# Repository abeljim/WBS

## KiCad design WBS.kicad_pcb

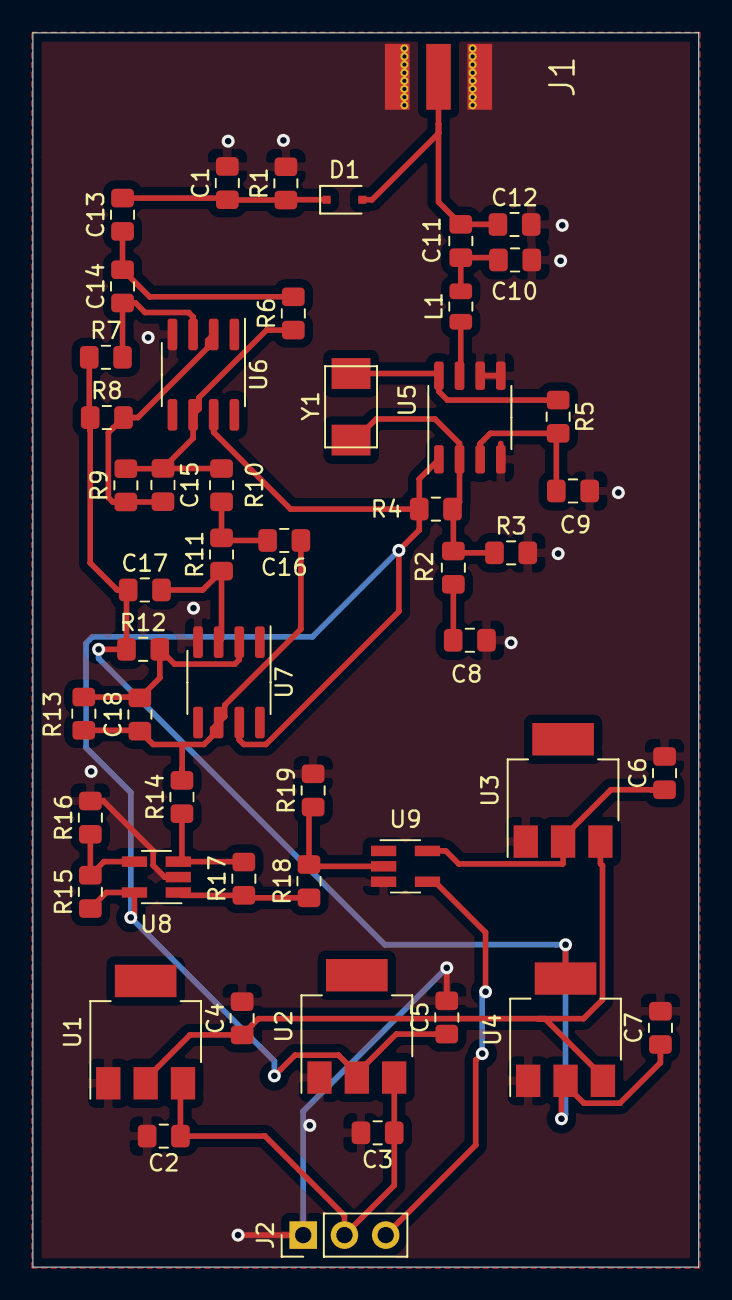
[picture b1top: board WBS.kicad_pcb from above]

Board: 2 copper layers, 41.0 x 76.0 mm, 51 parts (0 on the bottom side), 27 nets.

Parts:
C1, C10, C11, C12, C13, C14, C15, C16, C17, C18: C; C_0805_2012Metric_Pad1.15x1.40mm_HandSolder
C2, C3: 10u; C_0805_2012Metric_Pad1.15x1.40mm_HandSolder
C4, C5, C6: 22u; C_0805_2012Metric_Pad1.15x1.40mm_HandSolder
C7: 1u; C_0805_2012Metric_Pad1.15x1.40mm_HandSolder
C8: 820p; C_0805_2012Metric_Pad1.15x1.40mm_HandSolder
C9: 200pf; C_0805_2012Metric_Pad1.15x1.40mm_HandSolder
D1: D; D_SOD-323F
J1: Conn_Coaxial; CONSMA003.062
J2: Conn_01x03_Male; PinHeader_1x03_P2.54mm_Vertical
L1: L; L_0805_2012Metric
R1, R6, R7, R8, R9, R10, R11, R12, R13, R14, R15, R16, R17, R18, R19: R; R_0805_2012Metric_Pad1.15x1.40mm_HandSolder
R2: 22; R_0805_2012Metric_Pad1.15x1.40mm_HandSolder
R3, R4, R5: 2k; R_0805_2012Metric_Pad1.15x1.40mm_HandSolder
U1, U2: LT1117-5.0; SOT-223
U3: LT1117-3.3; SOT-223
U4: NCP1117-2.5_SOT223; SOT-223-3_TabPin2
U5: LT1016; SO-8_3.9x4.9mm_P1.27mm
U6, U7: OPA350; SOIC-8_3.9x4.9mm_P1.27mm
U8: TLV3201; SOT-23-5_HandSoldering
U9: SN74LVC1G04; SOT-23-5_HandSoldering
Y1: 13.56 Mhz; ECS-135.6-18-30-JEM-TR

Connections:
/2.5V: C7.1, C17.1, R7.1, R8.1, R12.1, U4.2
/3.3V: C6.1, U3.2, U9.5
/5V: C5.1, R4.1, R15.1, U2.2, U5.1, U6.7, U7.7, U8.5
/ADC/IN: C16.1, C18.1, R13.2, R14.2, U7.6
/ADC/OUT: J2.3, U9.4
/Bandpass/IN: C1.1, C13.2, D1.1, R1.1
/Oscillator/RF_OUT: C11.1, C12.1, D1.2, J1.1
/VBAT: C2.1, C3.1, J2.2, U1.3, U2.3
GND: C1.2, C2.2, C3.2, C4.2, C5.2, C6.2, C7.2, C8.2, C9.2, C10.2, C12.2, J1.2, J2.1, R1.2, R3.2, R16.2, R19.2, U1.1, U2.1, U3.1, U4.1, U5.4, U5.5, U5.6, U6.4, U7.4, U8.2, U9.3
unnamed: C4.1, U1.2, U3.3, U4.3
unnamed: C8.1, R2.2
unnamed: C9.1, R5.2, U5.3
unnamed: C10.1, C11.2, L1.2
unnamed: C13.1, C14.2, R6.2
unnamed: C14.1, R7.2, U6.3
unnamed: C15.1, R6.1, R9.2, R10.2, U6.6
unnamed: C15.2, R8.2, R9.1, U6.2
unnamed: C16.2, R10.1, R11.2
unnamed: C17.2, R11.1, U7.3
unnamed: C18.2, R12.2, R13.1, U7.2
unnamed: L1.1, U5.7
unnamed: R2.1, R3.1, R4.2, U5.2, Y1.1
unnamed: R5.1, U5.8, Y1.2
unnamed: R14.1, R17.2, U8.3
unnamed: R15.2, R16.1, U8.4
unnamed: R17.1, R18.1, U8.1
unnamed: R18.2, R19.1, U9.2

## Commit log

2019-10-29 added csv
2019-10-29 updated csv
